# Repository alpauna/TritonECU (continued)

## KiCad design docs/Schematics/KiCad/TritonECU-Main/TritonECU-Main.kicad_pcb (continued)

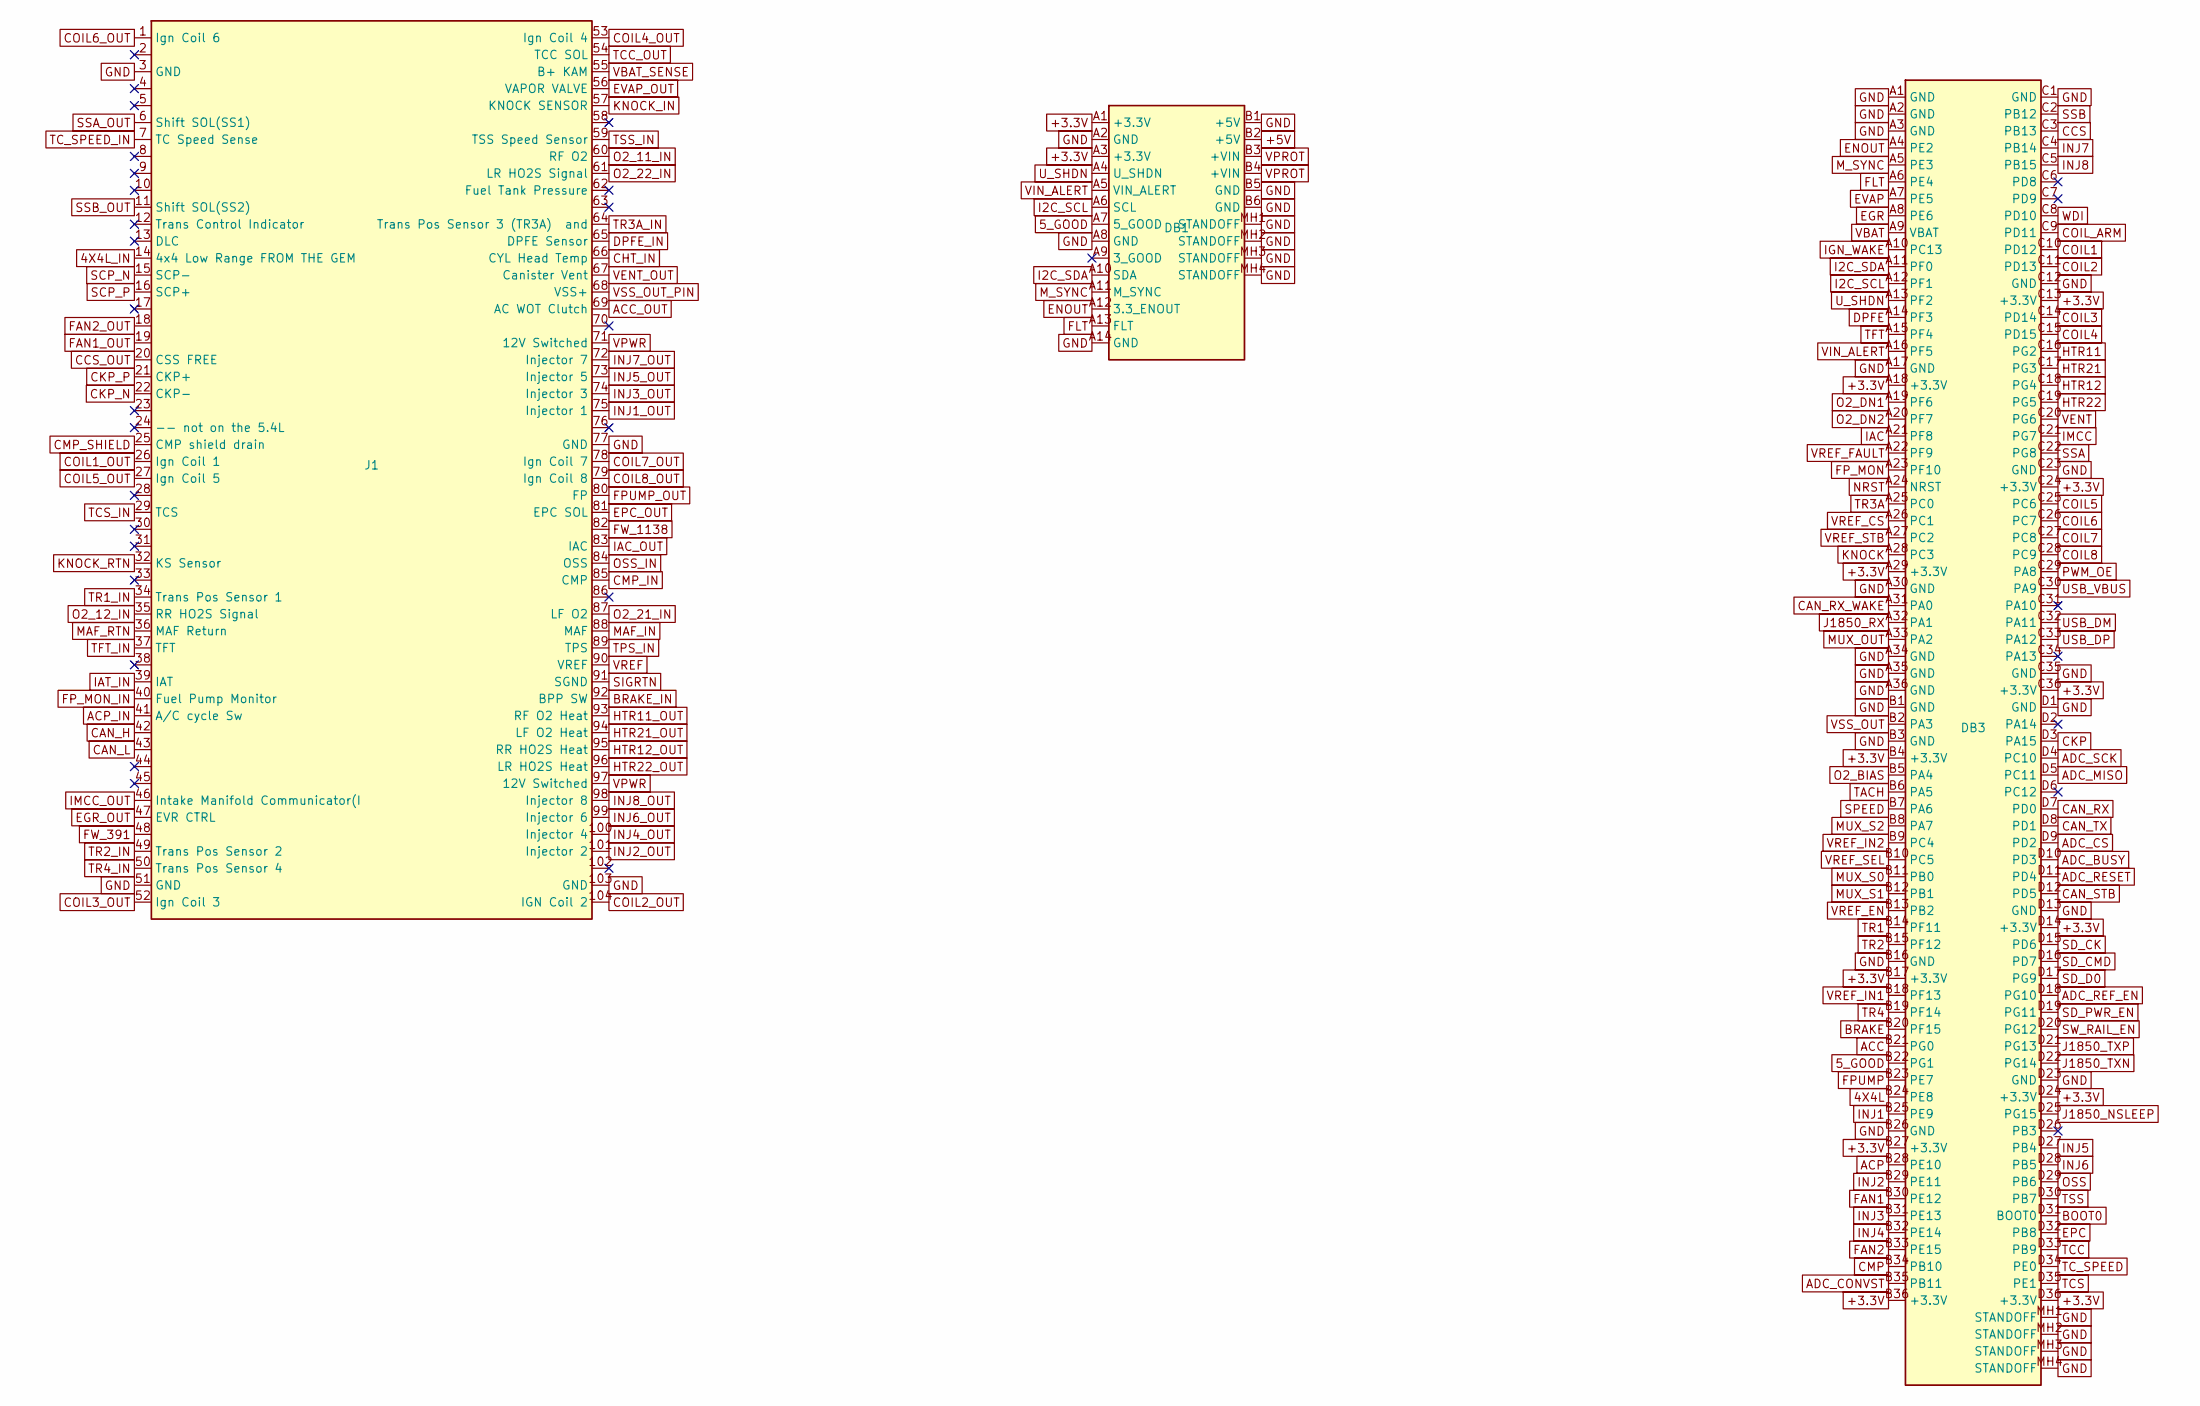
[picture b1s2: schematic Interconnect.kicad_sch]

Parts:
DB1: Power board V3; PowerBoard_V3_Mate
DB3: MCU module F767; MCUModule_F767_Mate
J1: EEC-V 104; EECV_104

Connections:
4X4L: DB3.B24 (PE8); also elsewhere on the board
4X4L_IN: J1.14 (4x4 Low Range FROM THE GEM); also elsewhere on the board
5_GOOD: DB1.A7 (5_GOOD), DB3.B22 (PG1)
+3.3V: DB1.A1 (+3.3V), DB1.A3 (+3.3V), DB3.A18 (+3.3V), DB3.A29 (+3.3V), DB3.B4 (+3.3V), DB3.B17 (+3.3V), DB3.B27 (+3.3V), DB3.B36 (+3.3V), DB3.C13 (+3.3V), DB3.C24 (+3.3V), DB3.C36 (+3.3V), DB3.D14 (+3.3V), DB3.D24 (+3.3V), DB3.D36 (+3.3V); also elsewhere on the board
+5V: DB1.B2 (+5V); also elsewhere on the board
ACC: DB3.B21 (PG0); also elsewhere on the board
ACC_OUT: J1.69 (AC WOT Clutch); also elsewhere on the board
ACP: DB3.B28 (PE10); also elsewhere on the board
ACP_IN: J1.41 (A/C cycle Sw); also elsewhere on the board
ADC_BUSY: DB3.D10 (PD3); also elsewhere on the board
ADC_CONVST: DB3.B35 (PB11); also elsewhere on the board
ADC_CS: DB3.D9 (PD2); also elsewhere on the board
ADC_MISO: DB3.D5 (PC11); also elsewhere on the board
ADC_REF_EN: DB3.D18 (PG10); also elsewhere on the board
ADC_RESET: DB3.D11 (PD4); also elsewhere on the board
ADC_SCK: DB3.D4 (PC10); also elsewhere on the board
BOOT0: DB3.D31 (BOOT0); also elsewhere on the board
BRAKE: DB3.B20 (PF15); also elsewhere on the board
BRAKE_IN: J1.92 (BPP SW); also elsewhere on the board
CAN_H: J1.42; also elsewhere on the board
CAN_L: J1.43; also elsewhere on the board
CAN_RX: DB3.D7 (PD0); also elsewhere on the board
CAN_RX_WAKE: DB3.A31 (PA0); also elsewhere on the board
CAN_STB: DB3.D12 (PD5); also elsewhere on the board
CAN_TX: DB3.D8 (PD1); also elsewhere on the board
CCS: DB3.C3 (PB13); also elsewhere on the board
CCS_OUT: J1.20 (CSS FREE); also elsewhere on the board
CHT_IN: J1.66 (CYL Head Temp); also elsewhere on the board
CKP: DB3.D3 (PA15); also elsewhere on the board
CKP_N: J1.22 (CKP-); also elsewhere on the board
CKP_P: J1.21 (CKP+); also elsewhere on the board
CMP: DB3.B34 (PB10); also elsewhere on the board
CMP_IN: J1.85 (CMP); also elsewhere on the board
CMP_SHIELD: J1.25 (CMP shield drain); also elsewhere on the board
COIL1: DB3.C10 (PD12); also elsewhere on the board
COIL1_OUT: J1.26 (Ign Coil 1); also elsewhere on the board
COIL2: DB3.C11 (PD13); also elsewhere on the board
COIL2_OUT: J1.104 (IGN Coil 2); also elsewhere on the board
COIL3: DB3.C14 (PD14); also elsewhere on the board
COIL3_OUT: J1.52 (Ign Coil 3); also elsewhere on the board
COIL4: DB3.C15 (PD15); also elsewhere on the board
COIL4_OUT: J1.53 (Ign Coil 4); also elsewhere on the board
COIL5: DB3.C25 (PC6); also elsewhere on the board
COIL5_OUT: J1.27 (Ign Coil 5); also elsewhere on the board
COIL6: DB3.C26 (PC7); also elsewhere on the board
COIL6_OUT: J1.1 (Ign Coil 6); also elsewhere on the board
COIL7: DB3.C27 (PC8); also elsewhere on the board
COIL7_OUT: J1.78 (Ign Coil 7); also elsewhere on the board
COIL8: DB3.C28 (PC9); also elsewhere on the board
COIL8_OUT: J1.79 (Ign Coil 8); also elsewhere on the board
COIL_ARM: DB3.C9 (PD11); also elsewhere on the board
DPFE: DB3.A14 (PF3); also elsewhere on the board
DPFE_IN: J1.65 (DPFE Sensor); also elsewhere on the board
EGR: DB3.A8 (PE6); also elsewhere on the board
EGR_OUT: J1.47 (EVR CTRL); also elsewhere on the board
ENOUT: DB1.A12 (3.3_ENOUT), DB3.A4 (PE2)
EPC: DB3.D32 (PB8); also elsewhere on the board
EPC_OUT: J1.81 (EPC SOL); also elsewhere on the board
EVAP: DB3.A7 (PE5); also elsewhere on the board
EVAP_OUT: J1.56 (VAPOR VALVE); also elsewhere on the board
FAN1: DB3.B30 (PE12); also elsewhere on the board
FAN1_OUT: J1.19; also elsewhere on the board
FAN2: DB3.B33 (PE15); also elsewhere on the board
FAN2_OUT: J1.18; also elsewhere on the board
FLT: DB1.A13 (FLT), DB3.A6 (PE4)
FPUMP: DB3.B23 (PE7); also elsewhere on the board
FPUMP_OUT: J1.80 (FP); also elsewhere on the board
FP_MON: DB3.A23 (PF10); also elsewhere on the board
FP_MON_IN: J1.40 (Fuel Pump Monitor); also elsewhere on the board
FW_391: J1.48; also elsewhere on the board
FW_1138: J1.82; also elsewhere on the board
GND: DB1.A2 (GND), DB1.A8 (GND), DB1.A14 (GND), DB1.B1 (+5V), DB1.B5 (GND), DB1.B6 (GND), DB1.MH1 (STANDOFF), DB1.MH2 (STANDOFF), DB1.MH3 (STANDOFF), DB1.MH4 (STANDOFF), DB3.A1 (GND), DB3.A2 (GND), DB3.A3 (GND), DB3.A17 (GND), DB3.A30 (GND), DB3.A34 (GND), DB3.A35 (GND), DB3.A36 (GND), DB3.B1 (GND), DB3.B3 (GND), DB3.B16 (GND), DB3.B26 (GND), DB3.C1 (GND), DB3.C12 (GND), DB3.C23 (GND), DB3.C35 (GND), DB3.D1 (GND), DB3.D13 (GND), DB3.D23 (GND), DB3.MH1 (STANDOFF), DB3.MH2 (STANDOFF), DB3.MH3 (STANDOFF), DB3.MH4 (STANDOFF), J1.3 (GND), J1.51 (GND), J1.77 (GND), J1.103 (GND); also elsewhere on the board
HTR11: DB3.C16 (PG2); also elsewhere on the board
HTR11_OUT: J1.93 (RF O2 Heat); also elsewhere on the board
HTR12: DB3.C18 (PG4); also elsewhere on the board
HTR12_OUT: J1.95 (RR HO2S Heat); also elsewhere on the board
HTR21: DB3.C17 (PG3); also elsewhere on the board
HTR21_OUT: J1.94 (LF O2 Heat); also elsewhere on the board
HTR22: DB3.C19 (PG5); also elsewhere on the board
HTR22_OUT: J1.96 (LR HO2S Heat); also elsewhere on the board
I2C_SCL: DB1.A6 (SCL), DB3.A12 (PF1)
I2C_SDA: DB1.A10 (SDA), DB3.A11 (PF0)
IAC: DB3.A21 (PF8); also elsewhere on the board
IAC_OUT: J1.83 (IAC); also elsewhere on the board
IAT_IN: J1.39 (IAT); also elsewhere on the board
IGN_WAKE: DB3.A10 (PC13); also elsewhere on the board
IMCC: DB3.C21 (PG7); also elsewhere on the board
IMCC_OUT: J1.46 (Intake Manifold Communicator(I); also elsewhere on the board
INJ1: DB3.B25 (PE9); also elsewhere on the board
INJ1_OUT: J1.75 (Injector 1); also elsewhere on the board
INJ2: DB3.B29 (PE11); also elsewhere on the board
INJ2_OUT: J1.101 (Injector 2); also elsewhere on the board
INJ3: DB3.B31 (PE13); also elsewhere on the board
INJ3_OUT: J1.74 (Injector 3); also elsewhere on the board
INJ4: DB3.B32 (PE14); also elsewhere on the board
INJ4_OUT: J1.100 (Injector 4); also elsewhere on the board
INJ5: DB3.D27 (PB4); also elsewhere on the board
INJ5_OUT: J1.73 (Injector 5); also elsewhere on the board
INJ6: DB3.D28 (PB5); also elsewhere on the board
INJ6_OUT: J1.99 (Injector 6); also elsewhere on the board
INJ7: DB3.C4 (PB14); also elsewhere on the board
INJ7_OUT: J1.72 (Injector 7); also elsewhere on the board
INJ8: DB3.C5 (PB15); also elsewhere on the board
INJ8_OUT: J1.98 (Injector 8); also elsewhere on the board
J1850_NSLEEP: DB3.D25 (PG15); also elsewhere on the board
J1850_RX: DB3.A32 (PA1); also elsewhere on the board
J1850_TXN: DB3.D22 (PG14); also elsewhere on the board
J1850_TXP: DB3.D21 (PG13); also elsewhere on the board
KNOCK: DB3.A28 (PC3); also elsewhere on the board
KNOCK_IN: J1.57 (KNOCK SENSOR); also elsewhere on the board
KNOCK_RTN: J1.32 (KS Sensor); also elsewhere on the board
MAF_IN: J1.88 (MAF); also elsewhere on the board
MAF_RTN: J1.36 (MAF Return); also elsewhere on the board
MUX_OUT: DB3.A33 (PA2); also elsewhere on the board
MUX_S0: DB3.B11 (PB0); also elsewhere on the board
MUX_S1: DB3.B12 (PB1); also elsewhere on the board
MUX_S2: DB3.B8 (PA7); also elsewhere on the board
M_SYNC: DB1.A11 (M_SYNC), DB3.A5 (PE3)
NRST: DB3.A24 (NRST); also elsewhere on the board
O2_11_IN: J1.60 (RF O2); also elsewhere on the board
O2_12_IN: J1.35 (RR HO2S Signal); also elsewhere on the board
O2_21_IN: J1.87 (LF O2); also elsewhere on the board
O2_22_IN: J1.61 (LR HO2S Signal); also elsewhere on the board
O2_BIAS: DB3.B5 (PA4); also elsewhere on the board
O2_DN1: DB3.A19 (PF6); also elsewhere on the board
O2_DN2: DB3.A20 (PF7); also elsewhere on the board
OSS: DB3.D29 (PB6); also elsewhere on the board
OSS_IN: J1.84 (OSS); also elsewhere on the board
PWM_OE: DB3.C29 (PA8); also elsewhere on the board
SCP_N: J1.15 (SCP-); also elsewhere on the board
SCP_P: J1.16 (SCP+); also elsewhere on the board
SD_CK: DB3.D15 (PD6); also elsewhere on the board
SD_CMD: DB3.D16 (PD7); also elsewhere on the board
SD_D0: DB3.D17 (PG9); also elsewhere on the board
SD_PWR_EN: DB3.D19 (PG11); also elsewhere on the board
SIGRTN: J1.91 (SGND); also elsewhere on the board
SPEED: DB3.B7 (PA6); also elsewhere on the board
SSA: DB3.C22 (PG8); also elsewhere on the board
SSA_OUT: J1.6 (Shift SOL(SS1)); also elsewhere on the board
SSB: DB3.C2 (PB12); also elsewhere on the board
SSB_OUT: J1.11 (Shift SOL(SS2)); also elsewhere on the board
SW_RAIL_EN: DB3.D20 (PG12); also elsewhere on the board
TACH: DB3.B6 (PA5); also elsewhere on the board
TCC: DB3.D33 (PB9); also elsewhere on the board
TCC_OUT: J1.54 (TCC SOL); also elsewhere on the board
TCS: DB3.D35 (PE1); also elsewhere on the board
TCS_IN: J1.29 (TCS); also elsewhere on the board
TC_SPEED: DB3.D34 (PE0); also elsewhere on the board
TC_SPEED_IN: J1.7 (TC Speed Sense); also elsewhere on the board
TFT: DB3.A15 (PF4); also elsewhere on the board
TFT_IN: J1.37 (TFT); also elsewhere on the board
TPS_IN: J1.89 (TPS); also elsewhere on the board
TR1: DB3.B14 (PF11); also elsewhere on the board
TR1_IN: J1.34 (Trans Pos Sensor 1); also elsewhere on the board
TR2: DB3.B15 (PF12); also elsewhere on the board
TR2_IN: J1.49 (Trans Pos Sensor 2); also elsewhere on the board
TR3A: DB3.A25 (PC0); also elsewhere on the board
TR3A_IN: J1.64 (Trans Pos Sensor 3 (TR3A) and); also elsewhere on the board
TR4: DB3.B19 (PF14); also elsewhere on the board
TR4_IN: J1.50 (Trans Pos Sensor 4); also elsewhere on the board
TSS: DB3.D30 (PB7); also elsewhere on the board
TSS_IN: J1.59 (TSS Speed Sensor); also elsewhere on the board
USB_DM: DB3.C32 (PA11); also elsewhere on the board
USB_DP: DB3.C33 (PA12); also elsewhere on the board
USB_VBUS: DB3.C30 (PA9); also elsewhere on the board
U_SHDN: DB1.A4 (U_SHDN), DB3.A13 (PF2)
VBAT: DB3.A9 (VBAT); also elsewhere on the board
VBAT_SENSE: J1.55 (B+ KAM); also elsewhere on the board
VENT: DB3.C20 (PG6); also elsewhere on the board
VENT_OUT: J1.67 (Canister Vent); also elsewhere on the board
VIN_ALERT: DB1.A5 (VIN_ALERT), DB3.A16 (PF5)
VPROT: DB1.B3 (+VIN), DB1.B4 (+VIN); also elsewhere on the board
VPWR: J1.71 (12V Switched), J1.97 (12V Switched); also elsewhere on the board
VREF: J1.90 (VREF); also elsewhere on the board
VREF_CS: DB3.A26 (PC1); also elsewhere on the board
VREF_EN: DB3.B13 (PB2); also elsewhere on the board
VREF_FAULT: DB3.A22 (PF9); also elsewhere on the board
VREF_IN1: DB3.B18 (PF13); also elsewhere on the board
VREF_IN2: DB3.B9 (PC4); also elsewhere on the board
VREF_SEL: DB3.B10 (PC5); also elsewhere on the board
VREF_STB: DB3.A27 (PC2); also elsewhere on the board
VSS_OUT: DB3.B2 (PA3); also elsewhere on the board
VSS_OUT_PIN: J1.68 (VSS+); also elsewhere on the board
WDI: DB3.C8 (PD10); also elsewhere on the board

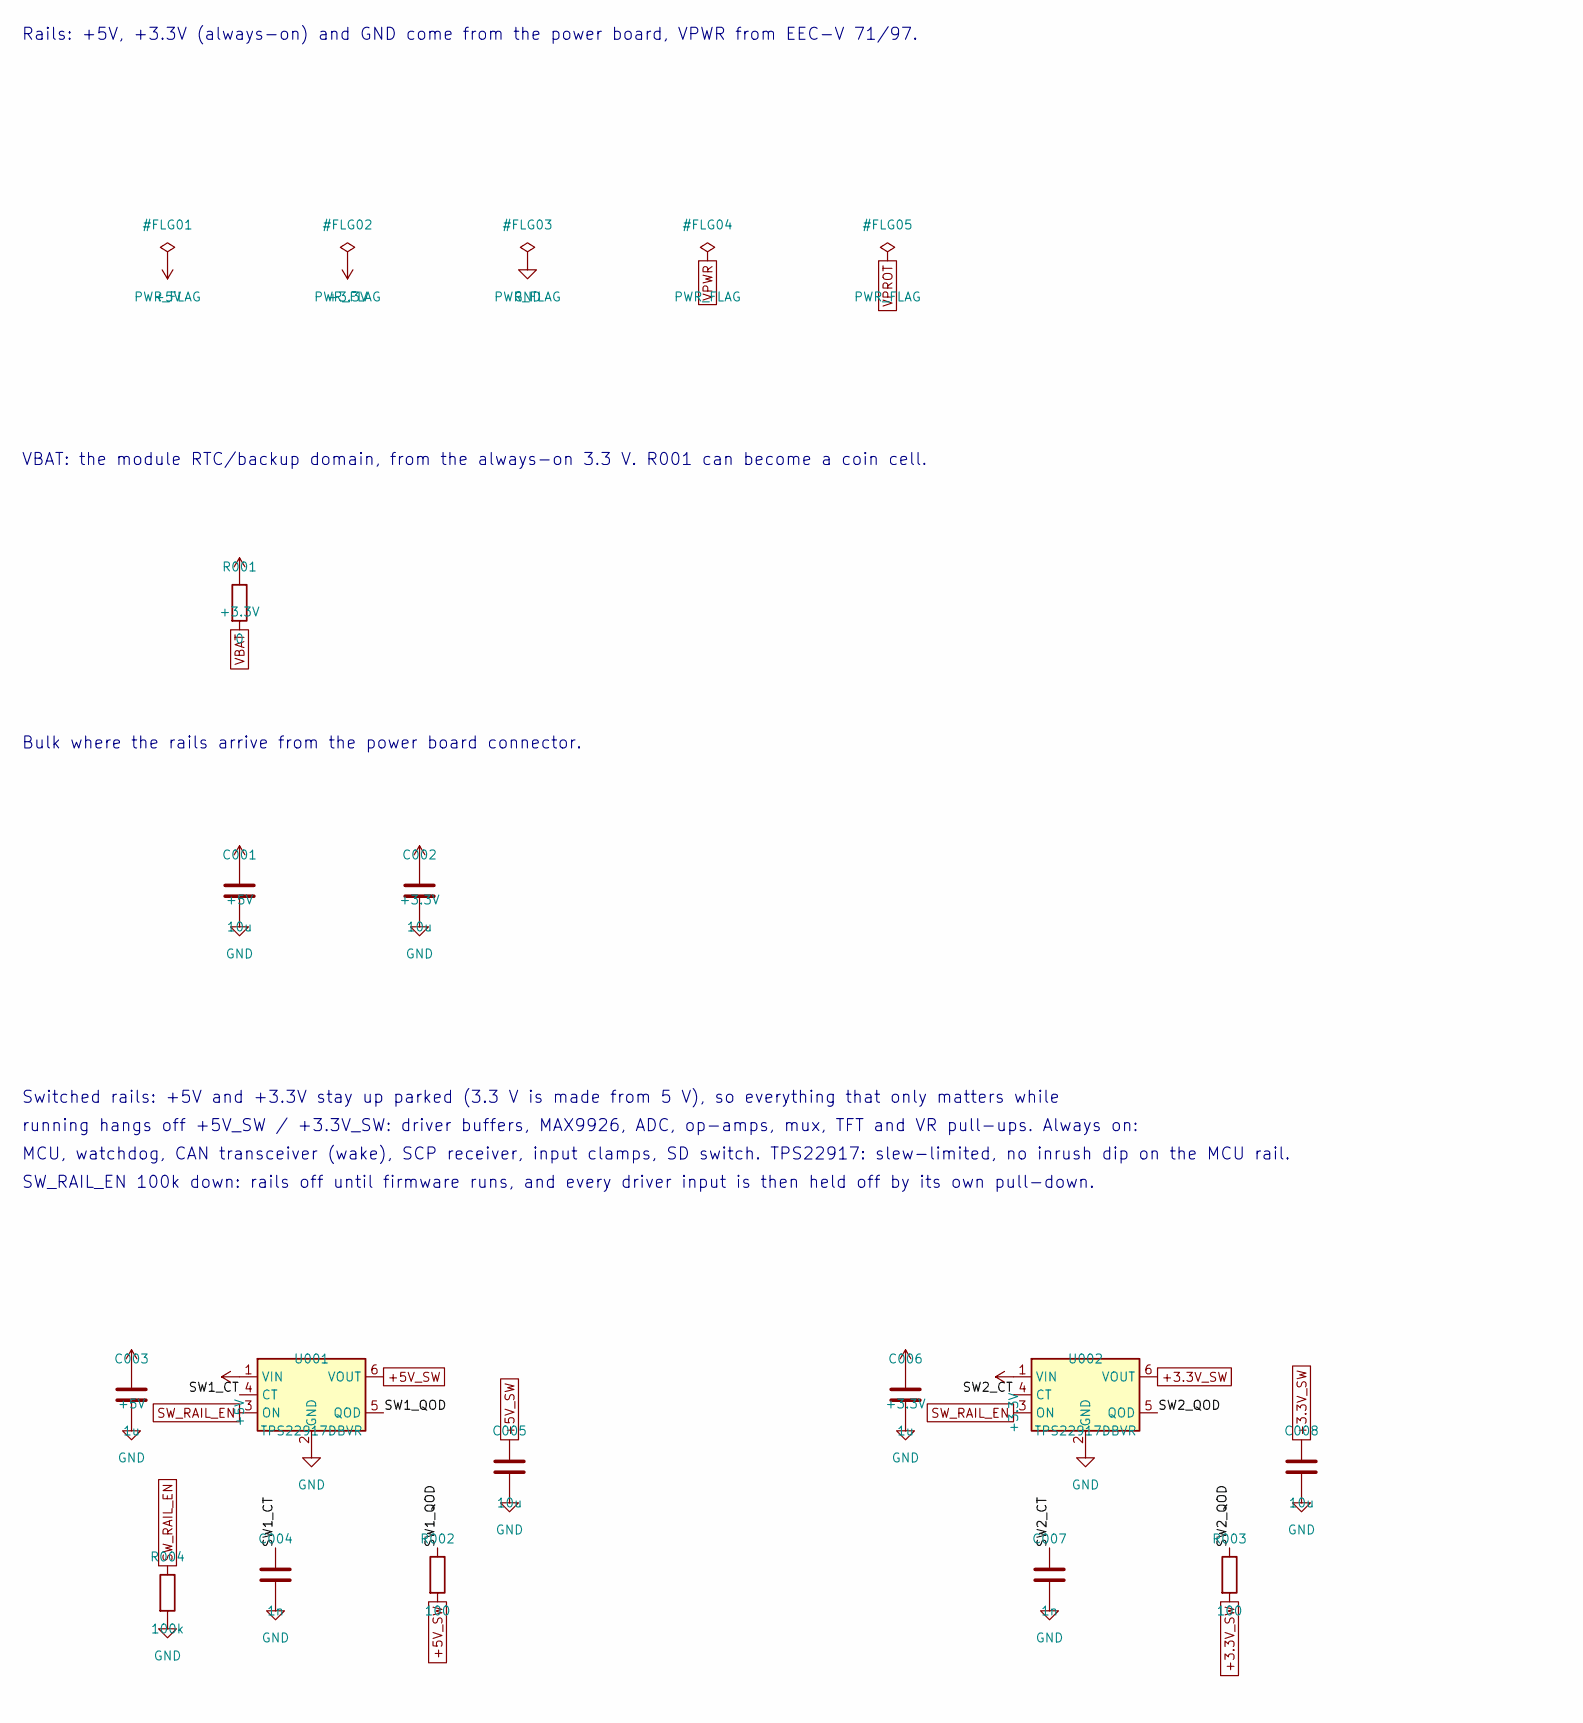
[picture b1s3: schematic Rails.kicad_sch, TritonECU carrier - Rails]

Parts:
C001, C002: 10u; C_1206_3216Metric_Pad1.33x1.80mm_HandSolder
C003, C006: 1u; C_0805_2012Metric_Pad1.18x1.45mm_HandSolder
C004, C007: 1n; C_0603_1608Metric_Pad1.08x0.95mm_HandSolder
C005, C008: 10u; C_0805_2012Metric_Pad1.18x1.45mm_HandSolder
R001: 0; R_0603_1608Metric_Pad0.98x0.95mm_HandSolder
R002, R003: 100; R_0603_1608Metric_Pad0.98x0.95mm_HandSolder
R004: 100k; R_0603_1608Metric_Pad0.98x0.95mm_HandSolder
U001, U002: TPS22917DBVR; SOT-23-6

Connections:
+3.3V: C002.1, C006.1, R001.1, U002.1 (VIN); also elsewhere on the board
+3.3V_SW: C008.1, R003.2, U002.6 (VOUT); also elsewhere on the board
+5V: C001.1, C003.1, U001.1 (VIN); also elsewhere on the board
+5V_SW: C005.1, R002.2, U001.6 (VOUT); also elsewhere on the board
/Rails/SW1_CT: C004.1, U001.4 (CT)
/Rails/SW1_QOD: R002.1, U001.5 (QOD)
/Rails/SW2_CT: C007.1, U002.4 (CT)
/Rails/SW2_QOD: R003.1, U002.5 (QOD)
GND: C001.2, C002.2, C003.2, C004.2, C005.2, C006.2, C007.2, C008.2, R004.2, U001.2 (GND), U002.2 (GND); also elsewhere on the board
SW_RAIL_EN: R004.1, U001.3 (ON), U002.3 (ON); also elsewhere on the board
VBAT: R001.2; also elsewhere on the board

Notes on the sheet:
Rails: +5V, +3.3V (always-on) and GND come from the power board, VPWR from EEC-V 71/97.
Bulk where the rails arrive from the power board connector.
Switched rails: +5V and +3.3V stay up parked (3.3 V is made from 5 V), so everything that only matters while
running hangs off +5V_SW / +3.3V_SW: driver buffers, MAX9926, ADC, op-amps, mux, TFT and VR pull-ups. Always on:
MCU, watchdog, CAN transceiver (wake), SCP receiver, input clamps, SD switch. TPS22917: slew-limited, no inrush dip on the MCU rail.
SW_RAIL_EN 100k down: rails off until firmware runs, and every driver input is then held off by its own pull-down.
VBAT: the module RTC/backup domain, from the always-on 3.3 V. R001 can become a coin cell.

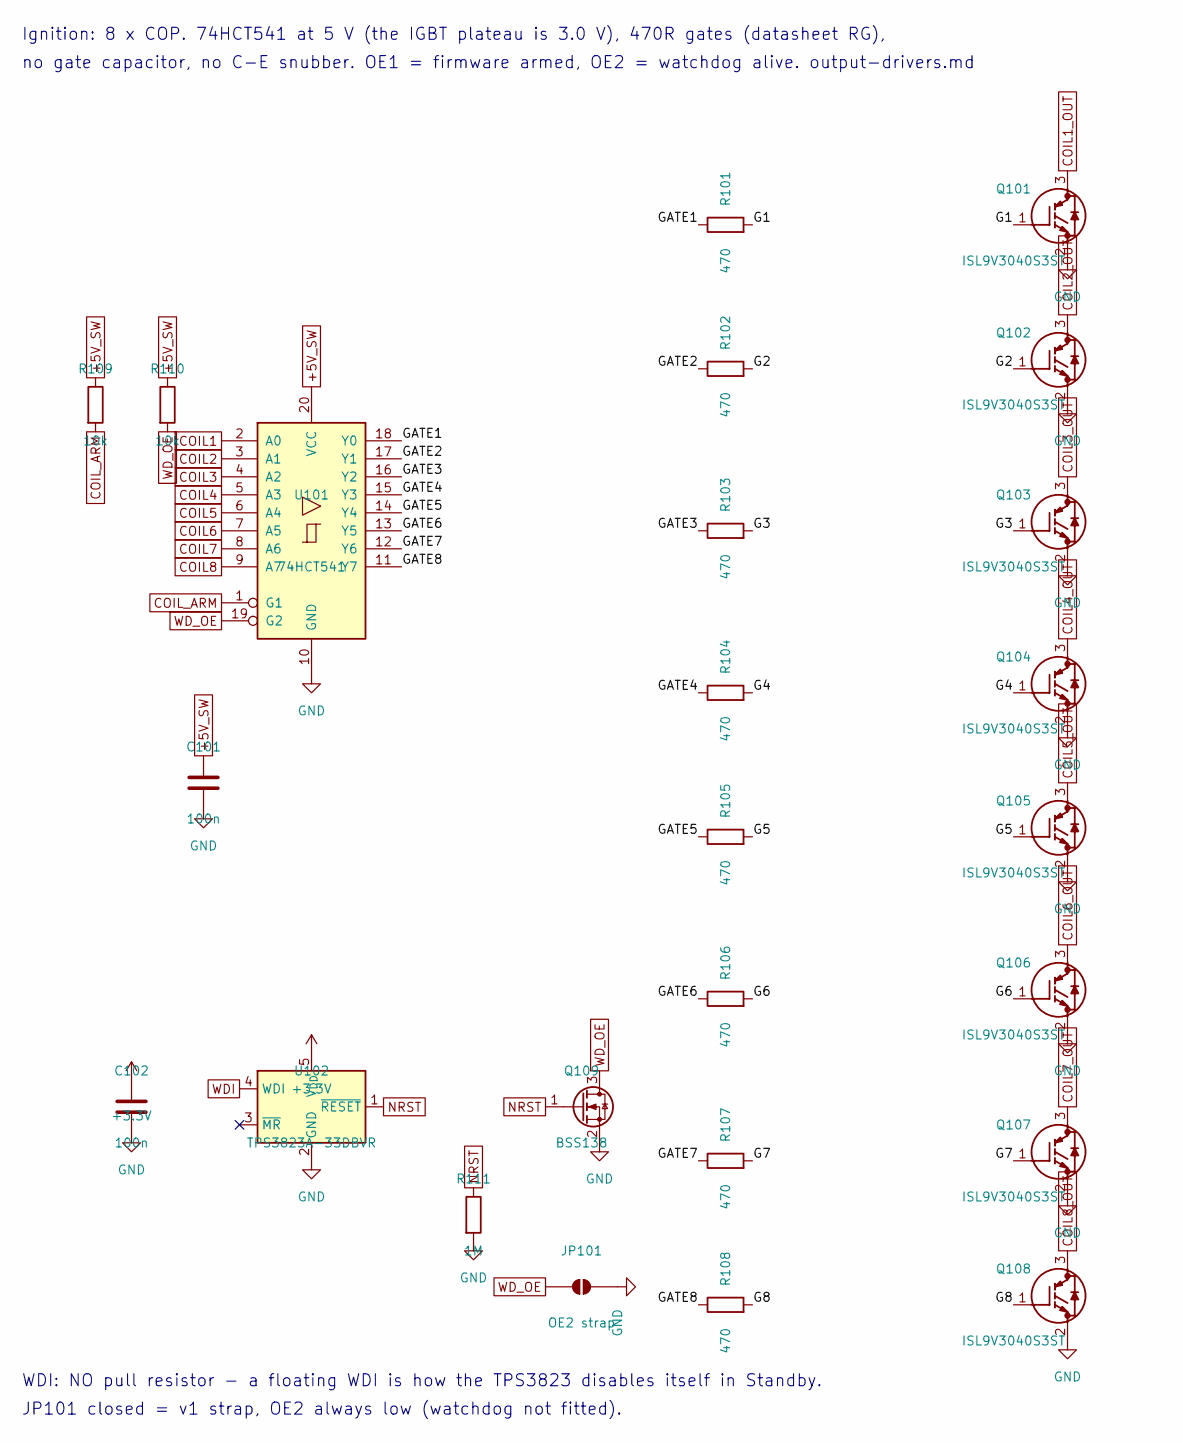
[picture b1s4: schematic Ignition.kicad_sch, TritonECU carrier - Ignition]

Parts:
C101, C102: 100n; C_0603_1608Metric_Pad1.08x0.95mm_HandSolder
JP101: OE2 strap; SolderJumper-2_P1.3mm_Open_RoundedPad1.0x1.5mm
Q101, Q102, Q103, Q104, Q105, Q106, Q107, Q108: ISL9V3040S3ST
Q109: BSS138; SOT-23
R101, R102, R103, R104, R105, R106, R107, R108: 470; R_0603_1608Metric_Pad0.98x0.95mm_HandSolder
R109, R110: 10k; R_0603_1608Metric_Pad0.98x0.95mm_HandSolder
R111: 1M; R_0603_1608Metric_Pad0.98x0.95mm_HandSolder
U101: 74HCT541; SOIC-20W_7.5x12.8mm_P1.27mm
U102: TPS3823A-33DBVR; SOT-23-5

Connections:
+3.3V: C102.1, U102.5 (V_{DD}); also elsewhere on the board
+5V_SW: C101.1, R109.1, R110.1, U101.20 (VCC); also elsewhere on the board
/Ignition/G1: Q101.1 (G), R101.2
/Ignition/G2: Q102.1 (G), R102.2
/Ignition/G3: Q103.1 (G), R103.2
/Ignition/G4: Q104.1 (G), R104.2
/Ignition/G5: Q105.1 (G), R105.2
/Ignition/G6: Q106.1 (G), R106.2
/Ignition/G7: Q107.1 (G), R107.2
/Ignition/G8: Q108.1 (G), R108.2
/Ignition/GATE1: R101.1, U101.18 (Y0)
/Ignition/GATE2: R102.1, U101.17 (Y1)
/Ignition/GATE3: R103.1, U101.16 (Y2)
/Ignition/GATE4: R104.1, U101.15 (Y3)
/Ignition/GATE5: R105.1, U101.14 (Y4)
/Ignition/GATE6: R106.1, U101.13 (Y5)
/Ignition/GATE7: R107.1, U101.12 (Y6)
/Ignition/GATE8: R108.1, U101.11 (Y7)
COIL1: U101.2 (A0); also elsewhere on the board
COIL1_OUT: Q101.3 (C); also elsewhere on the board
COIL2: U101.3 (A1); also elsewhere on the board
COIL2_OUT: Q102.3 (C); also elsewhere on the board
COIL3: U101.4 (A2); also elsewhere on the board
COIL3_OUT: Q103.3 (C); also elsewhere on the board
COIL4: U101.5 (A3); also elsewhere on the board
COIL4_OUT: Q104.3 (C); also elsewhere on the board
COIL5: U101.6 (A4); also elsewhere on the board
COIL5_OUT: Q105.3 (C); also elsewhere on the board
COIL6: U101.7 (A5); also elsewhere on the board
COIL6_OUT: Q106.3 (C); also elsewhere on the board
COIL7: U101.8 (A6); also elsewhere on the board
COIL7_OUT: Q107.3 (C); also elsewhere on the board
COIL8: U101.9 (A7); also elsewhere on the board
COIL8_OUT: Q108.3 (C); also elsewhere on the board
COIL_ARM: R109.2, U101.1 (G1); also elsewhere on the board
GND: C101.2, C102.2, JP101.2 (B), Q101.2 (E), Q102.2 (E), Q103.2 (E), Q104.2 (E), Q105.2 (E), Q106.2 (E), Q107.2 (E), Q108.2 (E), Q109.2 (S), R111.2, U101.10 (GND), U102.2 (GND); also elsewhere on the board
NRST: Q109.1 (G), R111.1, U102.1 (~RESET); also elsewhere on the board
WDI: U102.4 (WDI); also elsewhere on the board
WD_OE: JP101.1 (A), Q109.3 (D), R110.2, U101.19 (G2); also elsewhere on the board

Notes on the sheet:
Ignition: 8 x COP. 74HCT541 at 5 V (the IGBT plateau is 3.0 V), 470R gates (datasheet RG),
no gate capacitor, no C-E snubber. OE1 = firmware armed, OE2 = watchdog alive. output-drivers.md
WDI: NO pull resistor - a floating WDI is how the TPS3823 disables itself in Standby.
JP101 closed = v1 strap, OE2 always low (watchdog not fitted).

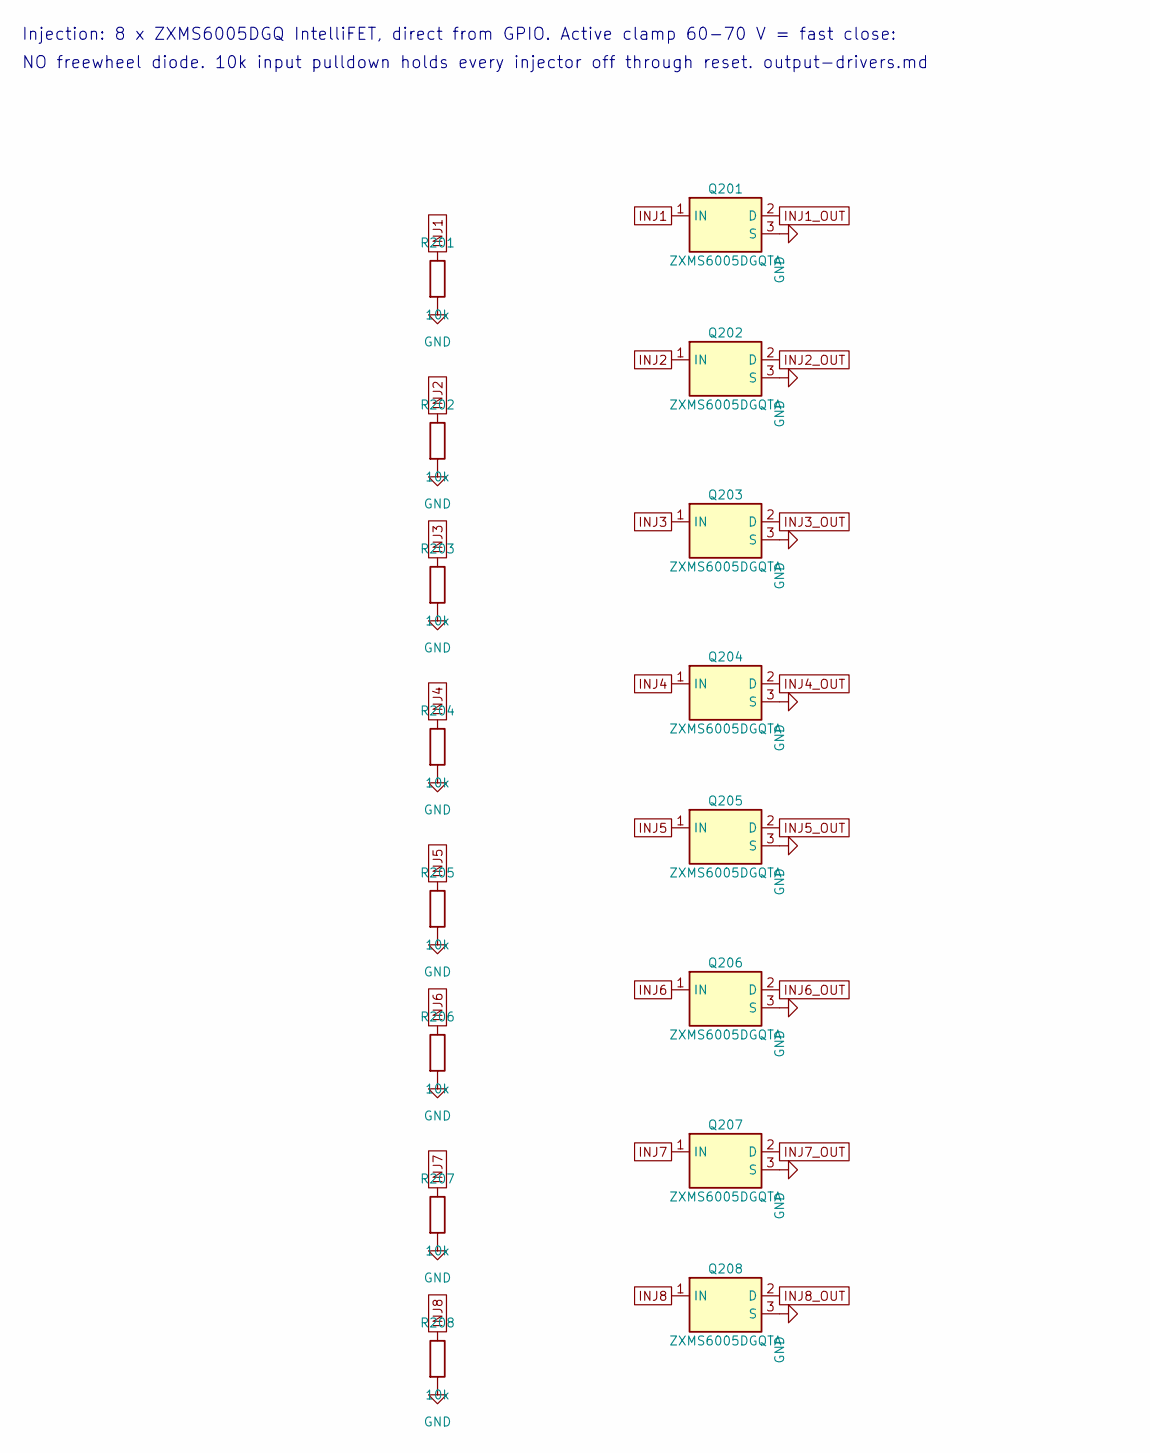
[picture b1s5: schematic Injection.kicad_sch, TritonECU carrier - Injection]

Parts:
Q201, Q202, Q203, Q204, Q205, Q206, Q207, Q208: ZXMS6005DGQTA; SOT-223-3_TabPin2
R201, R202, R203, R204, R205, R206, R207, R208: 10k; R_0603_1608Metric_Pad0.98x0.95mm_HandSolder

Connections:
GND: Q201.3 (S), Q202.3 (S), Q203.3 (S), Q204.3 (S), Q205.3 (S), Q206.3 (S), Q207.3 (S), Q208.3 (S), R201.2, R202.2, R203.2, R204.2, R205.2, R206.2, R207.2, R208.2; also elsewhere on the board
INJ1: Q201.1 (IN), R201.1; also elsewhere on the board
INJ1_OUT: Q201.2 (D); also elsewhere on the board
INJ2: Q202.1 (IN), R202.1; also elsewhere on the board
INJ2_OUT: Q202.2 (D); also elsewhere on the board
INJ3: Q203.1 (IN), R203.1; also elsewhere on the board
INJ3_OUT: Q203.2 (D); also elsewhere on the board
INJ4: Q204.1 (IN), R204.1; also elsewhere on the board
INJ4_OUT: Q204.2 (D); also elsewhere on the board
INJ5: Q205.1 (IN), R205.1; also elsewhere on the board
INJ5_OUT: Q205.2 (D); also elsewhere on the board
INJ6: Q206.1 (IN), R206.1; also elsewhere on the board
INJ6_OUT: Q206.2 (D); also elsewhere on the board
INJ7: Q207.1 (IN), R207.1; also elsewhere on the board
INJ7_OUT: Q207.2 (D); also elsewhere on the board
INJ8: Q208.1 (IN), R208.1; also elsewhere on the board
INJ8_OUT: Q208.2 (D); also elsewhere on the board

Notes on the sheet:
Injection: 8 x ZXMS6005DGQ IntelliFET, direct from GPIO. Active clamp 60-70 V = fast close:
NO freewheel diode. 10k input pulldown holds every injector off through reset. output-drivers.md
